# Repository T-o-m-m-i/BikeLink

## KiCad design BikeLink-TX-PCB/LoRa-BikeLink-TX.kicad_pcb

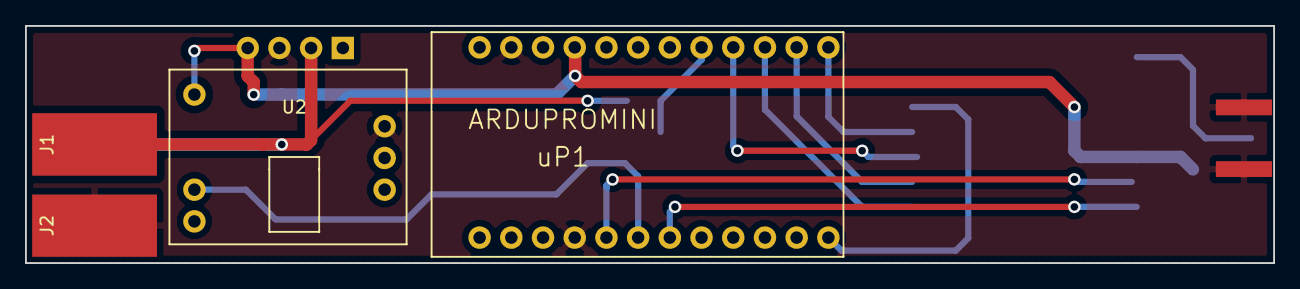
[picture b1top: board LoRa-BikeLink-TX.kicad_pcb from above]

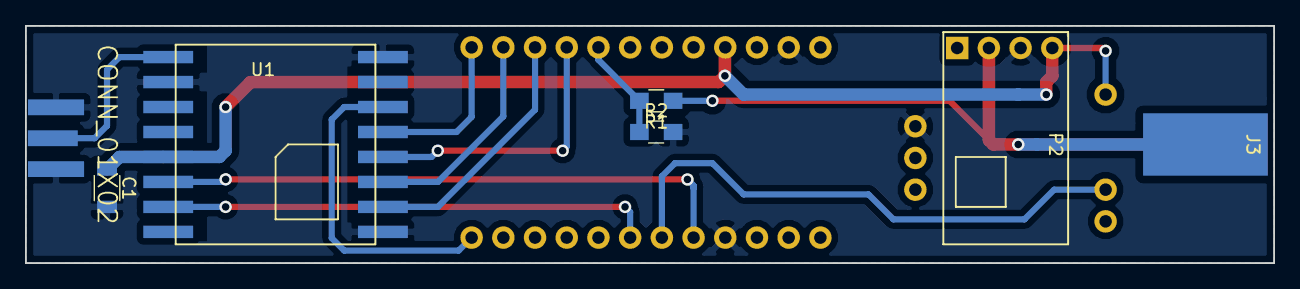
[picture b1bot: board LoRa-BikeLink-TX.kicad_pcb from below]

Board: 2 copper layers, 100.0 x 19.0 mm, 11 parts (7 on the bottom side), 15 nets.

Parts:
C1: 0.1u; C_1206
J1, J2, J3: CONN_01X01; SolderWirePad_single_SMD_5x10mm
P1: CONN_01X02; SMA_EDGE
P2: CONN_01X04; TPS61200_Tiny_Module
R1: 39k; R_0805_HandSoldering
R2: 120k; R_0805_HandSoldering
U1: RFM95
U2: ADXL345_brkout; ADXL345_BRKOUT
uP1: ARDUPROMINI; ArduProMini_only_sideholes

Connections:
/ACC_INT1: U2.4, uP1.12
/ADC_0: R1.2, R2.1, uP1.26
/BATT_IN: J1.1, J3.1, P2.3, R1.1
/I2C_SCL: U2.8, uP1.31
/I2C_SDA: U2.7, uP1.32
/Lora_DIO0: U1.14, uP1.11
/Lora_DIO1: U1.15, uP1.13
/Lora_MISO: U1.2, uP1.28
/Lora_MOSI: U1.3, uP1.29
/Lora_RESET: U1.6, uP1.18
/Lora_SCK: U1.4, uP1.27
/PWR_OUT: C1.1, P2.1, U1.13, U2.1, uP1.22
GND: C1.2, J2.1, P1.2, P2.2, R2.2, U1.1, U1.8, U1.10, U2.9, uP1.10, uP1.20
unnamed: P1.1, U1.9
unnamed: U1.5, uP1.30

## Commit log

2017-03-27 Some text
2017-04-26 1st code
2017-05-21 RHLib
2017-05-22 Display
2017-05-31 Sleep
2017-06-11 LED points
2017-10-03 Silent fixed
2018-03-14 PDFs
2018-05-09 ignore .bak files
